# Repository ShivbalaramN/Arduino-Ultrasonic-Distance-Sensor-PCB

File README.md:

**Arduino Ultrasonic Distance Sensor PCB**

**📌 Project Overview**

This project presents a custom PCB design for an ultrasonic distance measurement system using an Arduino Uno and the HC-SR04.
The PCB was designed using KiCad to interface the ultrasonic sensor with the Arduino board and provide output through an LED indicator.
The system measures the distance between the sensor and an object and triggers an LED when the object is within a predefined range.

**⚙️ Features**

Ultrasonic distance measurement

LED indication for nearby objects

Custom PCB designed in KiCad

Simple and low-cost hardware implementation

Beginner-friendly embedded system project

**🧩 Components Used**

Arduino Uno
HC-SR04
LED
Resistor (220Ω)
Power input connector
PCB designed using KiCad

**🔌 Pin Connections**
**
**Component   **                     **   Arduino Pin****
VCC                                    5V
GND                                    GND
TRIG                                   D9
ECHO                                   D10
LED                                    D7                      

**🖥️ Software Used**

KiCad – PCB design

Arduino IDE – Code development

**📂 Project Structure**

**Arduino-Ultrasonic-PCB**
│
├── Schematic
├── PCB_Layout
├── Gerber_Files
├── Arduino_Code
└── README.md

**🚀 Applications**
Obstacle detection

Distance measurement systems

Robotics projects

Smart parking systems

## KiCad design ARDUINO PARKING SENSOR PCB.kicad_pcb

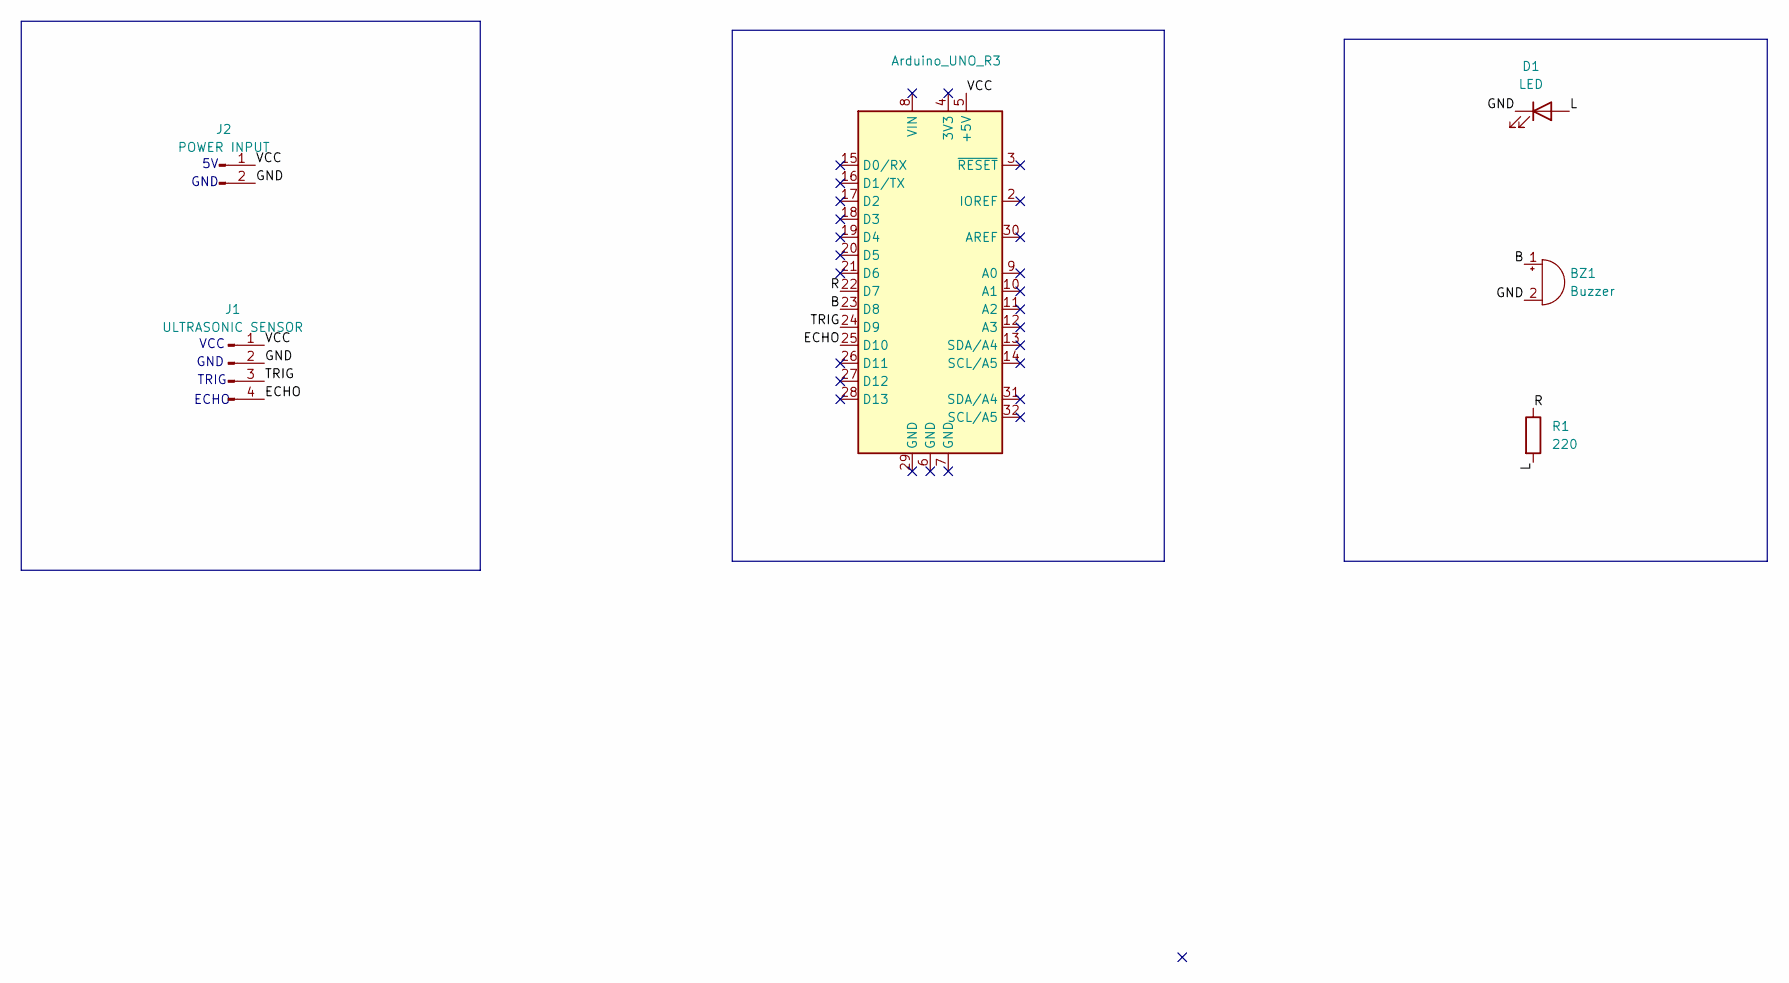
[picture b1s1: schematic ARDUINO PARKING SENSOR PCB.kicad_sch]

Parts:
A1: Arduino_UNO_R3
BZ1: Buzzer; Buzzer_12x9.5RM7.6
D1: LED; LED_D5.0mm
J1: ULTRASONIC SENSOR; PinHeader_1x04_P2.54mm_Vertical
J2: POWER INPUT; PhoenixContact_MCV_1,5_2-G-5.08_1x02_P5.08mm_Vertical
R1: 220; R_Axial_DIN0207_L6.3mm_D2.5mm_P7.62mm_Horizontal

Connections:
/B: A1.23 (D8), BZ1.1 (+)
/ECHO: A1.25 (D10), J1.4
/GND: BZ1.2 (-), D1.1 (K), J1.2, J2.2
/L: D1.2 (A), R1.2
/R: A1.22 (D7), R1.1
/TRIG: A1.24 (D9), J1.3
/VCC: A1.5 (+5V), J1.1, J2.1

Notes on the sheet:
VCC
GND
ECHO
TRIG

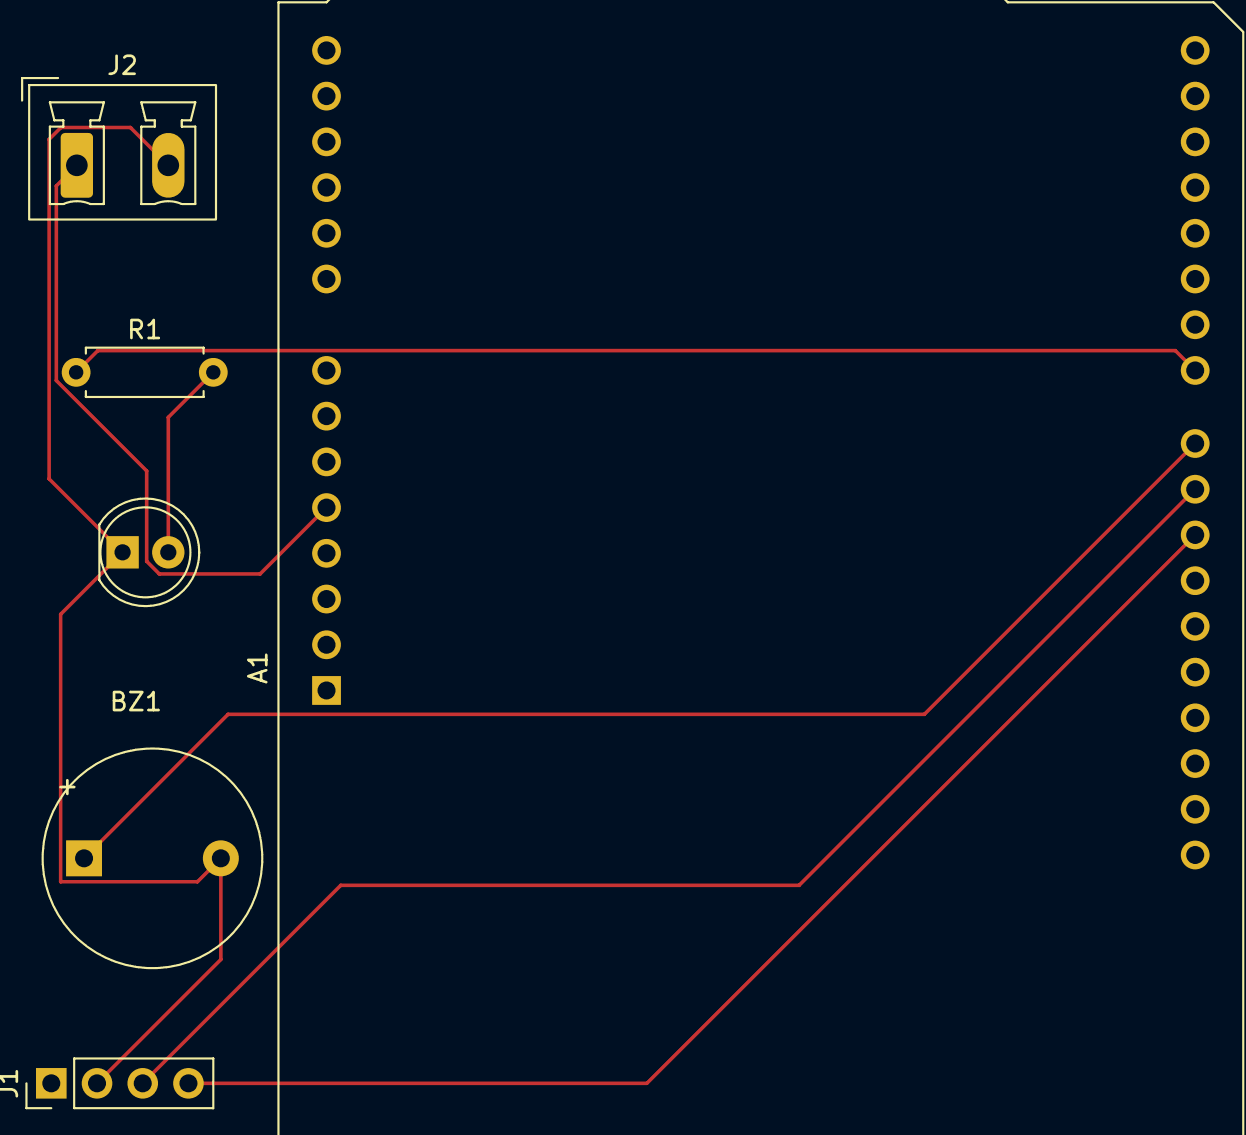
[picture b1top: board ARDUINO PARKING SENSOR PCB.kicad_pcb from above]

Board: 2 copper layers, 6 parts (0 on the bottom side), 7 nets.

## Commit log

2026-03-14 Update README with additional features and components
2026-03-14 Create ARDUINO CODING IN C++
